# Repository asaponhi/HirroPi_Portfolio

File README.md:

このリポジトリは整理がされておらず、
リポジトリMaizuru_Portfolioを見ていただきたいです。

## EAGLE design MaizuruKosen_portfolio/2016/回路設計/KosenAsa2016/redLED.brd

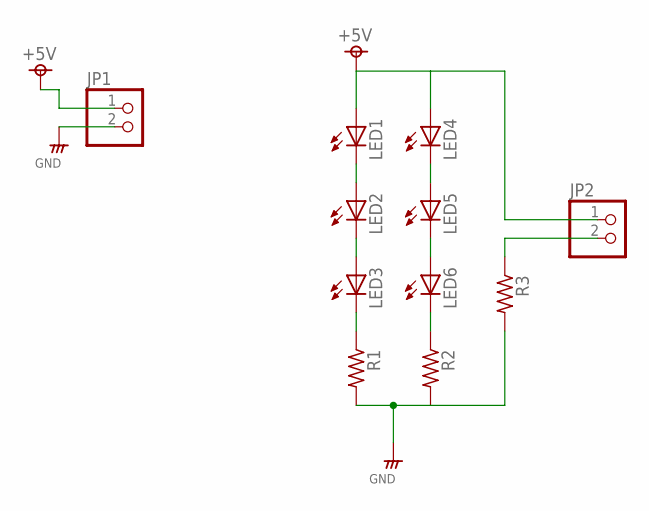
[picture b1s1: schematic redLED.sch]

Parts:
JP1, JP2: PINHD-1X2"; 1*02
LED1, LED2, LED3, LED4, LED5, LED6: LED5MM
R1, R2: RESISTORS-3; R_0.2
R3: RESISTORS-4; R_0.3

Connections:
+5V: JP1.1, JP2.1, LED1.A, LED4.A
GND: JP1.2, R1.2, R2.2, R3.2
unnamed: JP2.2, R3.1
unnamed: LED3.K (C), R1.1
unnamed: LED1.K (C), LED2.A
unnamed: LED2.K (C), LED3.A
unnamed: LED6.K (C), R2.1
unnamed: LED4.K (C), LED5.A
unnamed: LED5.K (C), LED6.A

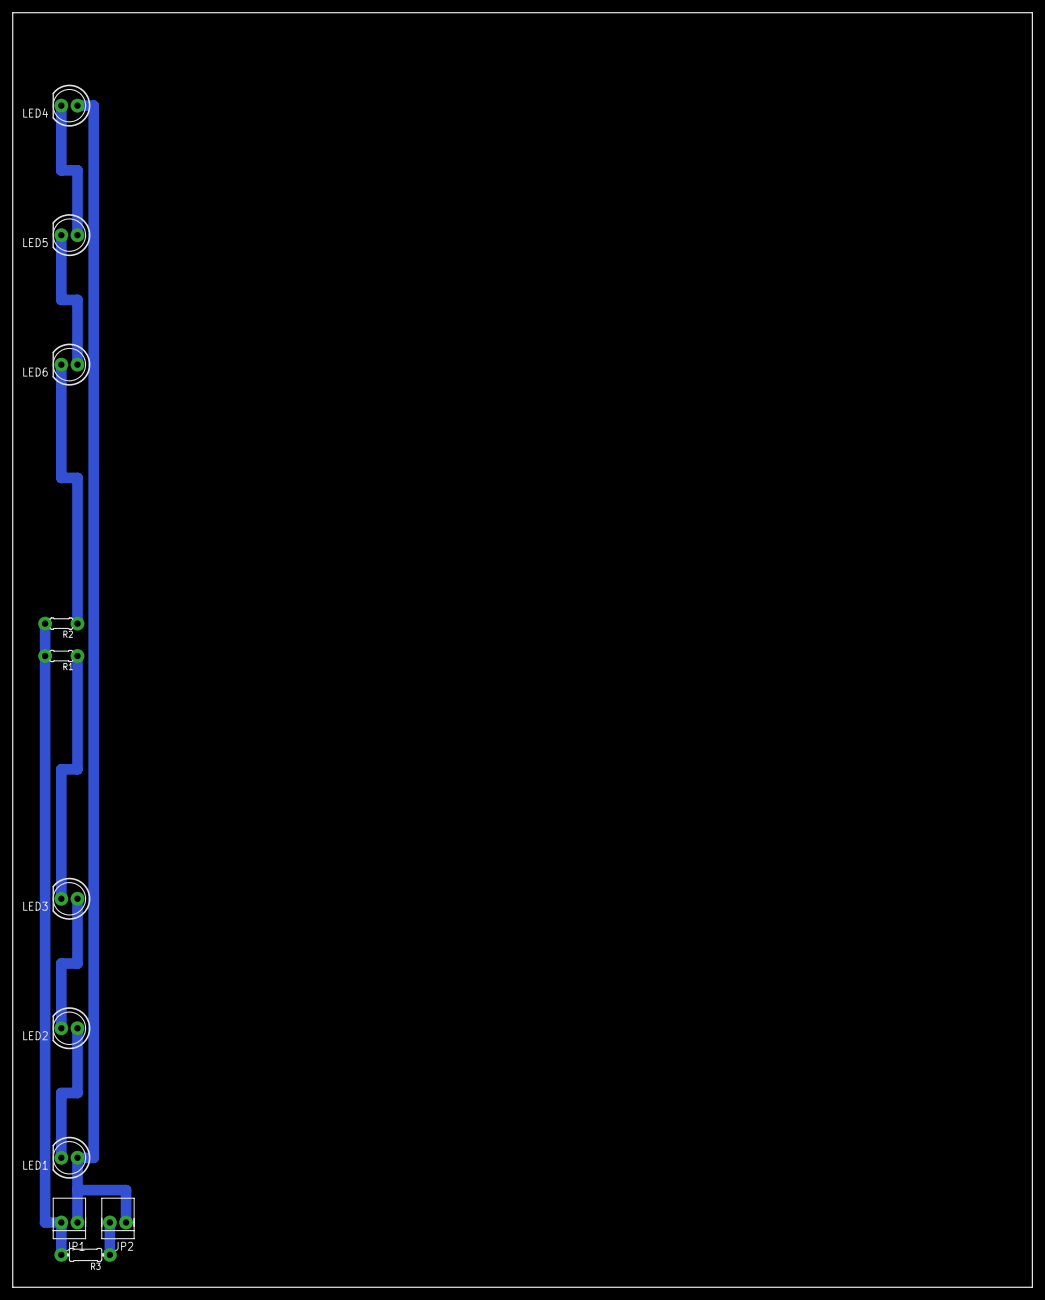
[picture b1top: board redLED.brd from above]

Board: 2 copper layers, 160.0 x 200.0 mm, 11 parts (0 on the bottom side), 9 nets.

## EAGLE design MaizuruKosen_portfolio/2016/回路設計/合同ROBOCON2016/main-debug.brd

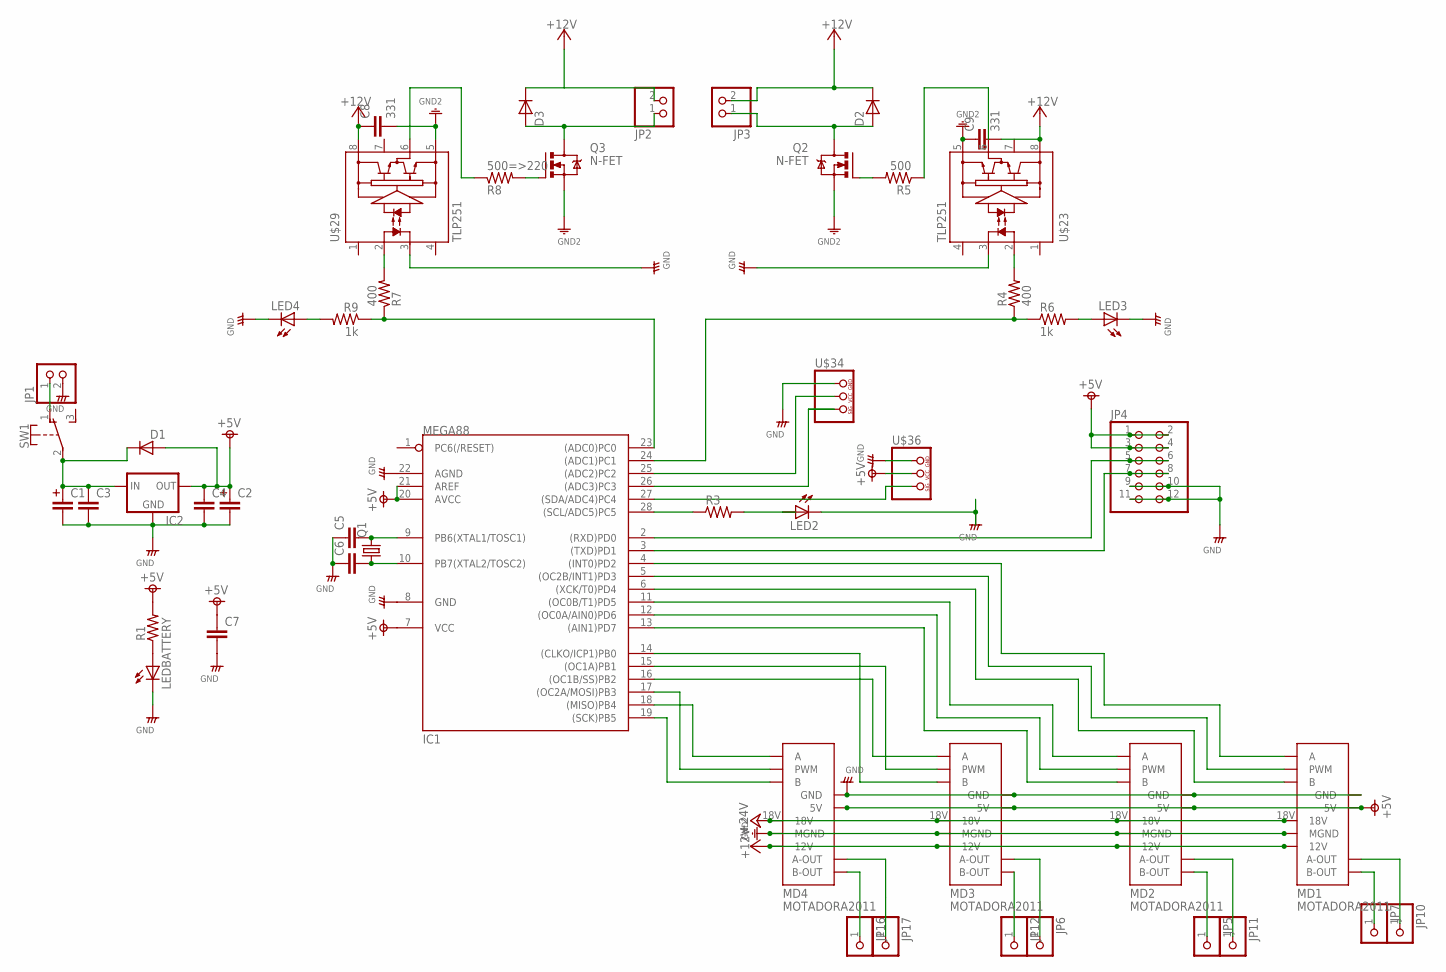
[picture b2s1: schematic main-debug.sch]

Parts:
C1, C2: CAPACITOR-330U; C_330U
C3, C4: MLCC-3; MLCC_50
C5, C6, C7: MLCC-2; MLCC_25
C8, C9: 331; MLCC_50
D1: DIODE_3
D2, D3: DIODE_4
IC1: MEGA88; DIL28-3
IC2: 78; 78XX
JP1: PINHD-1X2"; 1*02
JP2, JP3: PINHD-1X2; 1X02
JP4: PINHD-2X6; 2X06
JP5, JP6, JP7, JP10, JP11, JP12, JP16, JP17: PINHD-1X1; 1X01
LED2, LED3, LED4: LED5MM
LEDBATTERY: LED5MM
MD1, MD2, MD3, MD4: MOTADORA2011; MOTADORA2010
Q1: CTYSTALHC49/S; HC49/S
Q2, Q3: N-FET; TO-220V
R1, R3: RESISTORS-3; R_0.3
R4, R7: 400; R_0.3
R5: 500; R_0.3
R6, R9: 1k; R_0.3
R8: 500=>220; R_0.3
SW1: TOGGLE; 9450-2
U$23, U$29: TLP251; DIP8
U$34, U$36: PINHD-SENSOR; 1*03(KIKAKU)

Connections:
+5V: C2.P$1 (1), C4.1, C7.1, D1.A, IC1.7 (VCC), IC1.20 (AVCC), IC1.21 (AREF), IC2.P$3 (OUT), JP4.1, JP4.2, JP4.3, JP4.4, MD1.5V, MD2.5V, MD3.5V, MD4.5V, R1.2, U$36.VCC
+12V: C8.1, C9.2, D2.C, D3.C, JP2.2, JP3.2, MD1.12V, MD2.12V, MD3.12V, MD4.12V, U$23.8, U$29.8
+24V: MD1.18V, MD2.18V, MD3.18V, MD4.18V
GND: C1.P$2 (2), C2.P$2 (2), C3.2, C4.2, C5.1, C6.1, C7.2, IC1.8 (GND), IC1.22 (AGND), IC2.P$2 (GND), JP1.2, JP4.9, JP4.10, JP4.11, JP4.12, LED2.K (C), LED3.K (C), LED4.K (C), LEDBATTERY.K (C), MD1.GND, MD2.GND, MD3.GND, MD4.GND, U$23.3, U$29.3, U$34.GND, U$36.GND
GND12: C8.2, C9.1, MD1.MGND, MD2.MGND, MD3.MGND, MD4.MGND, Q2.3 (S), Q3.3 (S), U$23.5, U$29.5
unnamed: C5.2, IC1.9 (PB6(XTAL1/TOSC1)), Q1.2
unnamed: C6.2, IC1.10 (PB7(XTAL2/TOSC2)), Q1.1
unnamed: JP1.1, SW1.1 (O)
unnamed: C1.P$1 (1), C3.1, D1.C, IC2.P$1 (IN), SW1.2
unnamed: IC1.27 ((SDA/ADC4)PC4), U$36.SIG
unnamed: IC1.23 ((ADC0)PC0), R7.1, R9.1
unnamed: IC1.24 ((ADC1)PC1), R4.1, R6.1
unnamed: IC1.2 ((RXD)PD0), JP4.5, JP4.6
unnamed: IC1.18 ((MISO)PB4), MD4.A
unnamed: IC1.6 ((XCK/T0)PD4), MD1.B
unnamed: IC1.4 ((INT0)PD2), MD1.A
unnamed: IC1.19 ((SCK)PB5), MD4.B
unnamed: IC1.3 ((TXD)PD1), JP4.7, JP4.8
unnamed: IC1.28 ((SCL/ADC5)PC5), R3.1
unnamed: IC1.5 ((OC2B/INT1)PD3), MD1.PWM
unnamed: IC1.17 ((OC2A/MOSI)PB3), MD4.PWM
unnamed: IC1.16 ((OC1B/SS)PB2), MD3.A
unnamed: IC1.15 ((OC1A)PB1), MD3.PWM
unnamed: IC1.14 ((CLKO/ICP1)PB0), MD3.B
unnamed: IC1.13 ((AIN1)PD7), MD2.B
unnamed: IC1.12 ((OC0A/AIN0)PD6), MD2.PWM
unnamed: IC1.11 ((OC0B/T1)PD5), MD2.A
unnamed: JP12.1, MD3.B-OUT
unnamed: JP6.1, MD3.A-OUT
unnamed: JP11.1, MD2.A-OUT
unnamed: JP7.1, MD1.B-OUT
unnamed: JP10.1, MD1.A-OUT
unnamed: D3.A, JP2.1, Q3.2 (D)
unnamed: Q2.1 (G), R5.2
unnamed: JP5.1, MD2.B-OUT
unnamed: JP16.1, MD4.B-OUT
unnamed: JP17.1, MD4.A-OUT
unnamed: D2.A, JP3.1, Q2.2 (D)
unnamed: R4.2, U$23.2
unnamed: R5.1, U$23.6
unnamed: LED3.A, R6.2
unnamed: LEDBATTERY.A, R1.1
unnamed: Q3.1 (G), R8.2
unnamed: IC1.25 ((ADC2)PC2), U$34.VCC
unnamed: R7.2, U$29.2
unnamed: R8.1, U$29.6
unnamed: LED4.A, R9.2
unnamed: IC1.26 ((ADC3)PC3), U$34.SIG
unnamed: LED2.A, R3.2

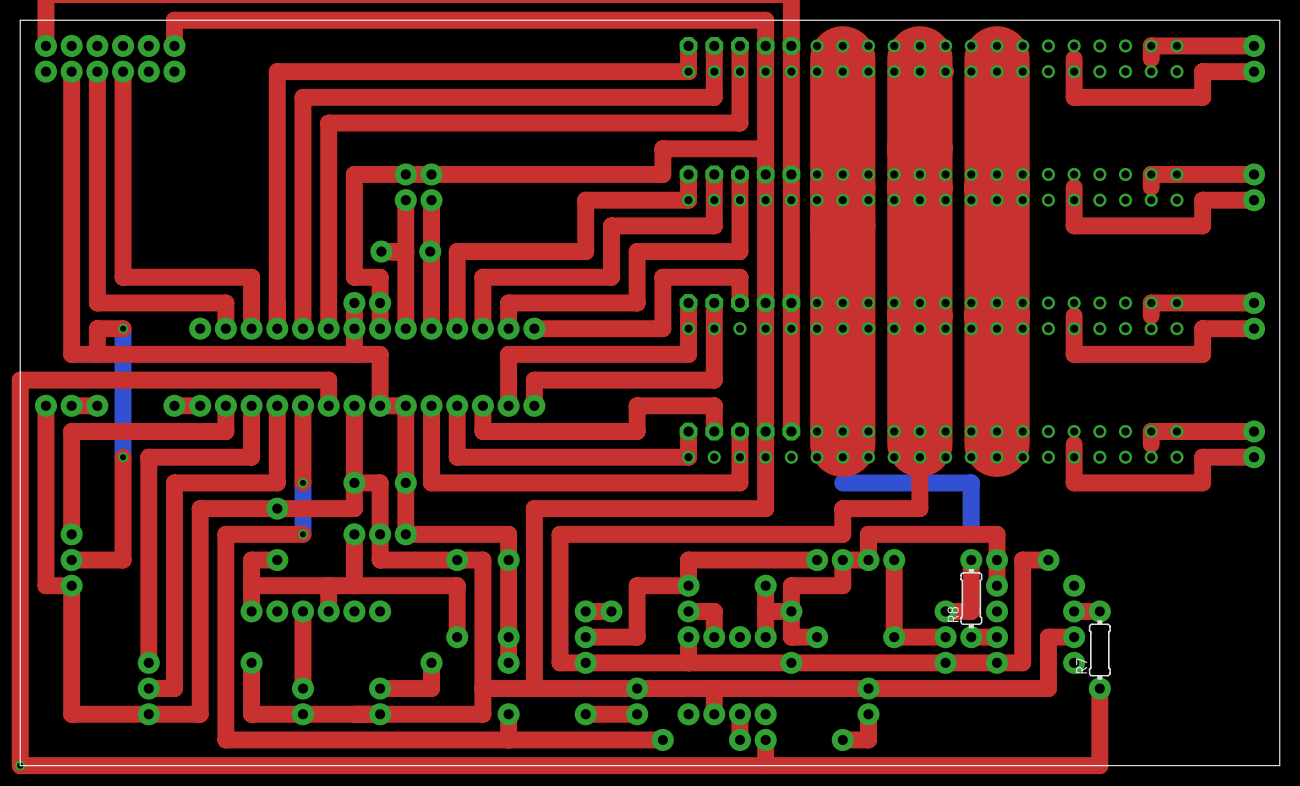
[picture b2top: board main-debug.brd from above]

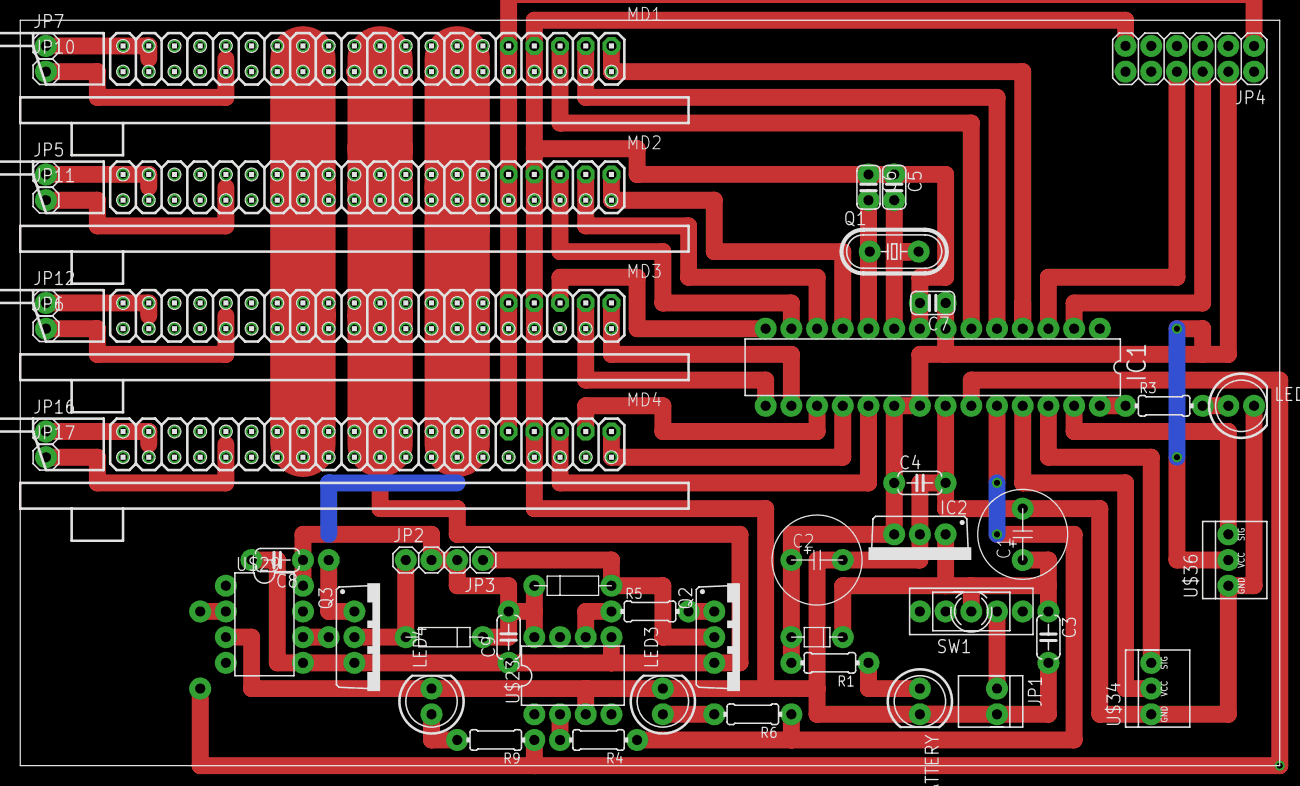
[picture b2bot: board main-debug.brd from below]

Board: 2 copper layers, 124.5 x 73.7 mm, 50 parts (48 on the bottom side), 49 nets.

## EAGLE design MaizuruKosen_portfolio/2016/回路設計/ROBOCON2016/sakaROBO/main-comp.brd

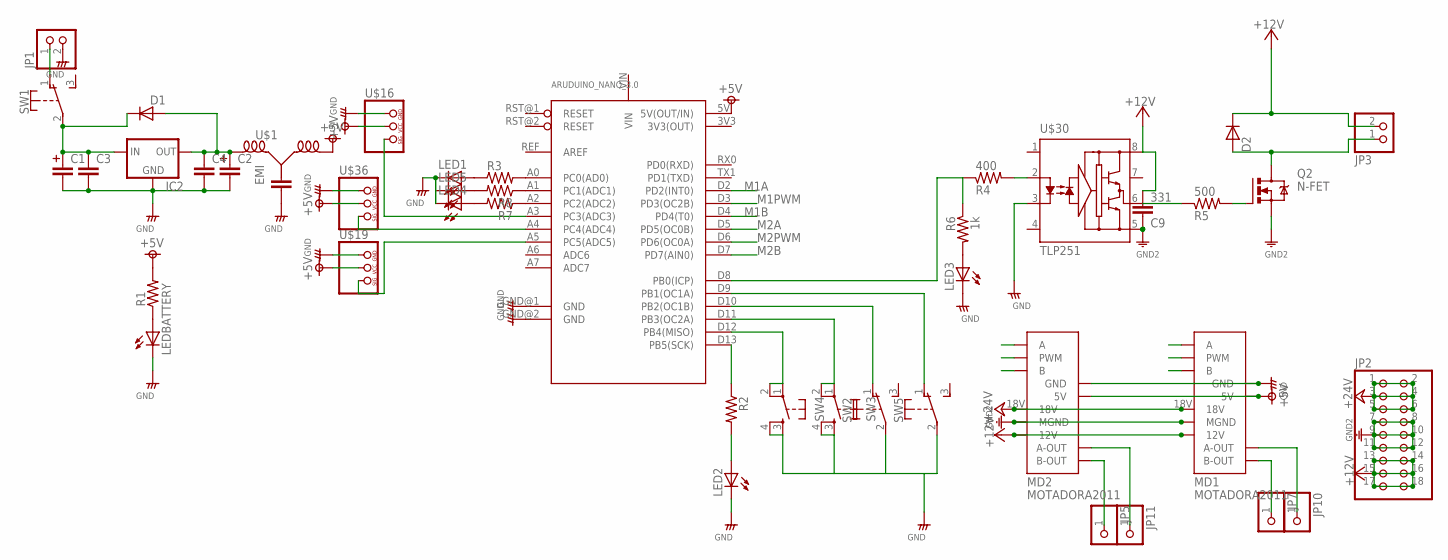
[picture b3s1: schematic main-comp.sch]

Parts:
C1, C2: CAPACITOR-330U; C_330U
C3, C4: MLCC-3; MLCC_50
C9: 331; MLCC_50
D1: DIODE_3
D2: DIODE_4
IC2: 78; 78XX
JP1: PINHD-1X2"; 1*02
JP2: PINHD-2X9; 2X09
JP3: PINHD-1X2; 1X02
JP5, JP7, JP10, JP11: PINHD-1X1; 1X01
LED1, LED2, LED3, LED4, LED5: LED3MM
LEDBATTERY: LED5MM
MD1, MD2: MOTADORA2011; MOTADORA2010
Q2: N-FET; TO-220V
R1: RESISTORS-2; R_0.2
R2, R3, R7, R8: RESISTORS3216; 3216
R4: 400; R_0.2
R5: 500; 3216
R6: 1k; 3216
SW1, SW2, SW5: TOGGLE; 9450-2
SW3, SW4: TACTB3F; B3F-10XX
U$1: EMI; EMI_3
U$14: ARUDUINO_NANO_3.0; ARYDUINO_NANO_3.0
U$16, U$19, U$36: PINHD-SENSOR; 1*03(KIKAKU)
U$30: TLP251; DIP8

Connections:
+5V: MD1.5V, MD2.5V, R1.2, U$1.3, U$14.5V (5V(OUT/IN)), U$16.VCC, U$19.VCC, U$36.VCC
+12V: C9.2, D2.C, JP2.13, JP2.14, JP2.15, JP2.16, JP2.17, JP2.18, JP3.2, MD1.12V, MD2.12V, U$30.8
+24V: JP2.1, JP2.2, JP2.3, JP2.4, JP2.5, JP2.6, MD1.18V, MD2.18V
GND: C1.P$2 (2), C2.P$2 (2), C3.2, C4.2, IC2.P$2 (GND), JP1.2, LED1.K (C), LED2.K (C), LED3.K (C), LED4.K (C), LED5.K (C), LEDBATTERY.K (C), MD1.GND, MD2.GND, SW2.2, SW3.3 (S), SW3.4 (S1), SW4.3 (S), SW4.4 (S1), SW5.2, U$1.2, U$14.GND@1 (GND), U$14.GND@2 (GND), U$16.GND, U$19.GND, U$30.3, U$36.GND
GND12: C9.1, JP2.7, JP2.8, JP2.9, JP2.10, JP2.11, JP2.12, MD1.MGND, MD2.MGND, Q2.3 (S), U$30.5
M1A: MD1.A, U$14.D2 (PD2(INT0))
M1B: MD1.B, U$14.D4 (PD4(T0))
M1PWM: MD1.PWM, U$14.D3 (PD3(OC2B))
M2A: MD2.A, U$14.D5 (PD5(OC0B))
M2B: MD2.B, U$14.D7 (PD7(AIN0))
M2PWM: MD2.PWM, U$14.D6 (PD6(OC0A))
unnamed: U$14.A3 (PC3(ADC3)), U$16.SIG
unnamed: R3.2, U$14.A0 (PC0(AD0))
unnamed: JP1.1, SW1.1 (O)
unnamed: U$14.A4 (PC4(ADC4)), U$36.SIG
unnamed: C1.P$1 (1), C3.1, D1.C, IC2.P$1 (IN), SW1.2
unnamed: U$14.A5 (PC5(ADC5)), U$19.SIG
unnamed: LED4.A, R7.2
unnamed: R4.1, R6.1, U$14.D8 (PB0(ICP))
unnamed: C2.P$1 (1), C4.1, D1.A, IC2.P$3 (OUT), U$1.1
unnamed: R8.1, U$14.A1 (PC1(ADC1))
unnamed: LED1.A, R3.1
unnamed: SW2.1 (O), U$14.D10 (PB2(OC1B))
unnamed: SW5.1 (O), U$14.D9 (PB1(OC1A))
unnamed: R2.1, U$14.D13 (PB5(SCK))
unnamed: R7.1, U$14.A2 (PC2(ADC2))
unnamed: SW4.1, SW4.2 (P1), U$14.D12 (PB4(MISO))
unnamed: LEDBATTERY.A, R1.1
unnamed: SW3.1, SW3.2 (P1), U$14.D11 (PB3(OC2A))
unnamed: LED2.A, R2.2
unnamed: LED5.A, R8.2
unnamed: JP11.1, MD2.A-OUT
unnamed: JP7.1, MD1.B-OUT
unnamed: JP10.1, MD1.A-OUT
unnamed: Q2.1 (G), R5.2
unnamed: JP5.1, MD2.B-OUT
unnamed: D2.A, JP3.1, Q2.2 (D)
unnamed: R4.2, U$30.2
unnamed: R5.1, U$30.6
unnamed: LED3.A, R6.2

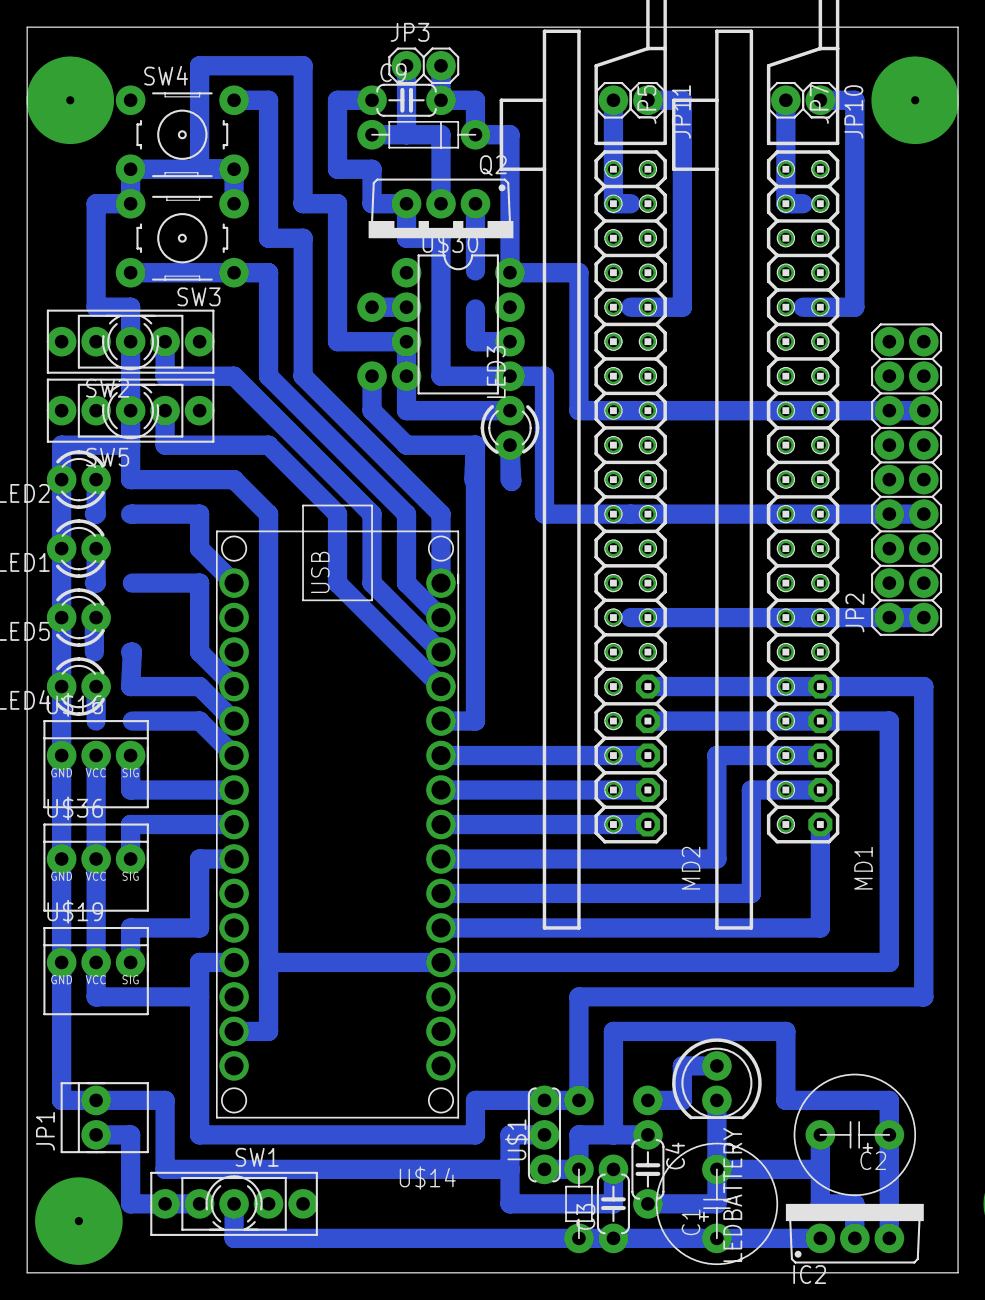
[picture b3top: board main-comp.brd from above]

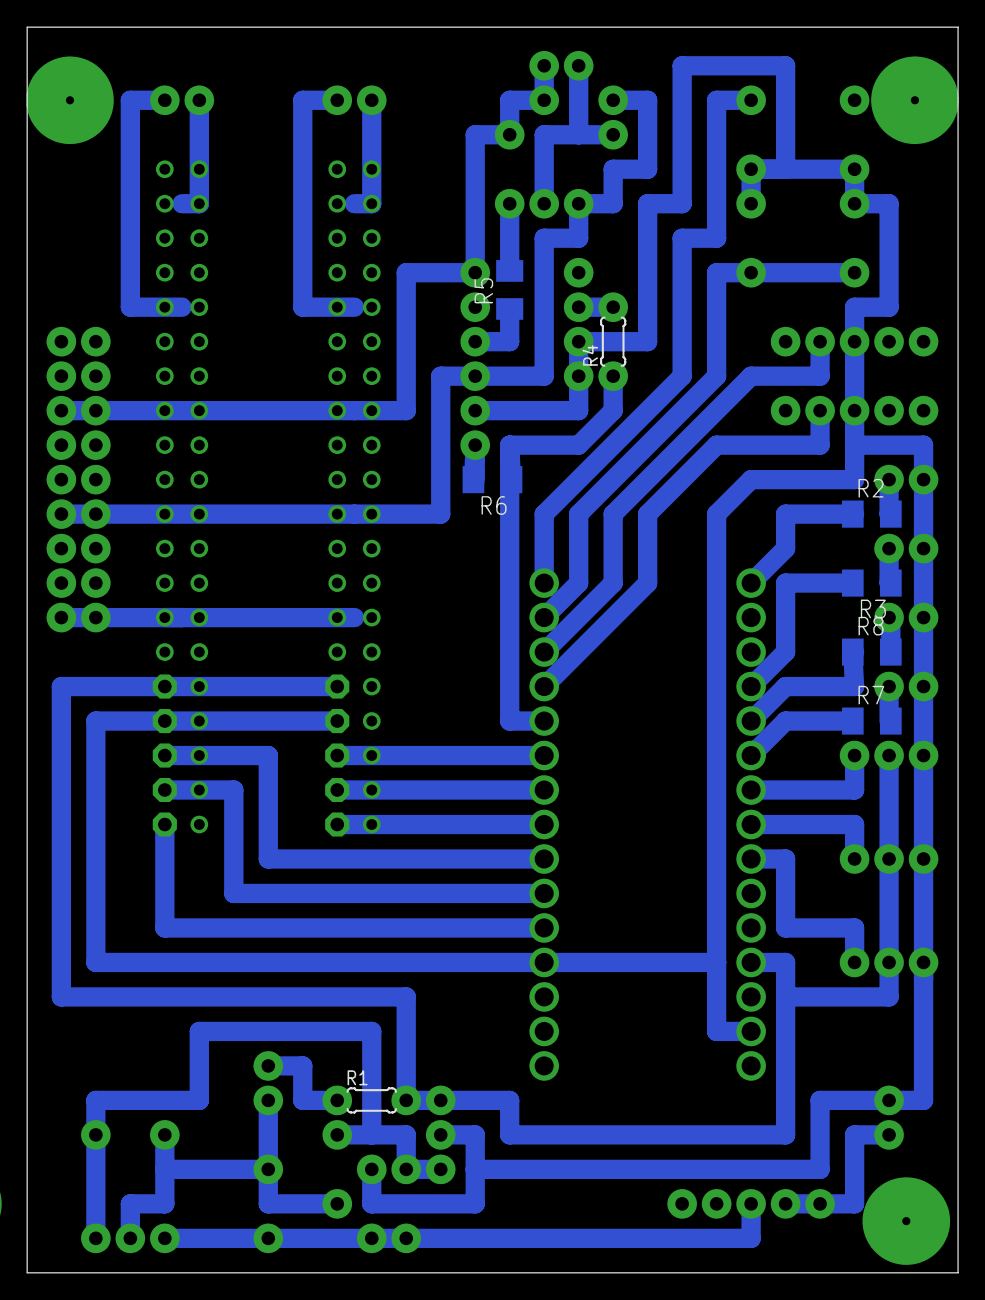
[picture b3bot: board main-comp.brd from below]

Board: 2 copper layers, 68.6 x 91.7 mm, 43 parts (8 on the bottom side), 40 nets.

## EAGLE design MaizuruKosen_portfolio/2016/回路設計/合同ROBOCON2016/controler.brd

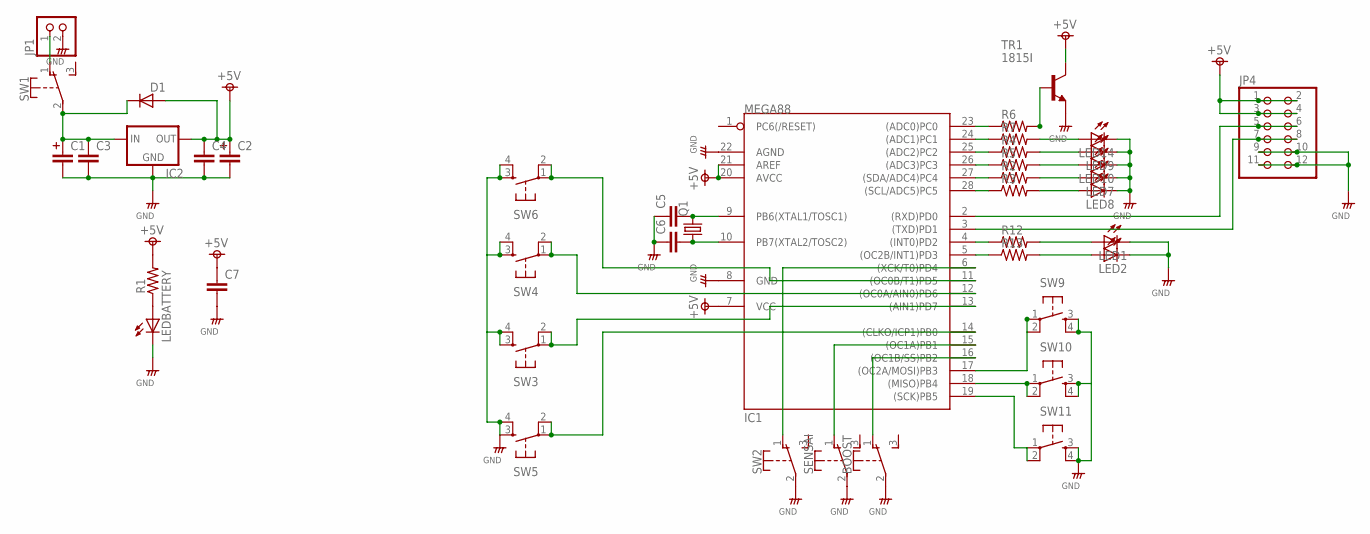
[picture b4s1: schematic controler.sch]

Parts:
BOOST: TOGGLE; 9450-2
C1, C2: CAPACITOR-330U; C_330U
C3, C4, C7: MLCC-3; MLCC_50
C5, C6: MLCC-2; MLCC_25
D1: DIODE_3
IC1: MEGA88; DIL28-3
IC2: 78; 78XX
JP1: PINHD-1X2"; 1*02
JP4: PINHD-2X6; 2X06
LED1, LED2, LED7, LED8, LED9, LED10, LED14: LED3MM
LEDBATTERY: LED5MM
Q1: CTYSTALHC49/S; HC49/S
R1, R6: RESISTORS-2; R_0.2
R2, R3, R4, R5, R7, R12, R13: RESISTORS-1; R_0.1
SENSAI: TOGGLE; 9450-2
SW1, SW2: TOGGLE; 9450-2
SW3, SW4, SW5, SW6, SW9, SW10, SW11: TACT; 1273
TR1: 1815I; TO92A

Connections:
+5V: C2.P$1 (1), C4.1, C7.1, D1.A, IC1.7 (VCC), IC1.20 (AVCC), IC1.21 (AREF), IC2.P$3 (OUT), JP4.1, JP4.2, JP4.3, JP4.4, R1.2, TR1.C
GND: BOOST.2, C1.P$2 (2), C2.P$2 (2), C3.2, C4.2, C5.1, C6.1, C7.2, IC1.8 (GND), IC1.22 (AGND), IC2.P$2 (GND), JP1.2, JP4.9, JP4.10, JP4.11, JP4.12, LED1.K (C), LED2.K (C), LED7.K (C), LED8.K (C), LED9.K (C), LED10.K (C), LED14.K (C), LEDBATTERY.K (C), SENSAI.2, SW2.2, SW3.3 (S), SW3.4 (S1), SW4.3 (S), SW4.4 (S1), SW5.3 (S), SW5.4 (S1), SW6.3 (S), SW6.4 (S1), SW9.3 (S), SW9.4 (S1), SW10.3 (S), SW10.4 (S1), SW11.3 (S), SW11.4 (S1), TR1.E
unnamed: C5.2, IC1.9 (PB6(XTAL1/TOSC1)), Q1.2
unnamed: C6.2, IC1.10 (PB7(XTAL2/TOSC2)), Q1.1
unnamed: JP1.1, SW1.1 (O)
unnamed: IC1.4 ((INT0)PD2), R12.1
unnamed: C1.P$1 (1), C3.1, D1.C, IC2.P$1 (IN), SW1.2
unnamed: IC1.5 ((OC2B/INT1)PD3), R13.1
unnamed: LED2.A, R13.2
unnamed: LED1.A, R12.2
unnamed: IC1.2 ((RXD)PD0), JP4.5, JP4.6
unnamed: IC1.25 ((ADC2)PC2), R4.1
unnamed: IC1.26 ((ADC3)PC3), R5.1
unnamed: R6.2, TR1.B
unnamed: IC1.23 ((ADC0)PC0), R6.1
unnamed: IC1.3 ((TXD)PD1), JP4.7, JP4.8
unnamed: IC1.27 ((SDA/ADC4)PC4), R2.1
unnamed: IC1.28 ((SCL/ADC5)PC5), R3.1
unnamed: IC1.24 ((ADC1)PC1), R7.1
unnamed: IC1.6 ((XCK/T0)PD4), SW2.1 (O)
unnamed: IC1.11 ((OC0B/T1)PD5), SW6.1, SW6.2 (P1)
unnamed: IC1.12 ((OC0A/AIN0)PD6), SW4.1, SW4.2 (P1)
unnamed: IC1.13 ((AIN1)PD7), SW3.1, SW3.2 (P1)
unnamed: IC1.14 ((CLKO/ICP1)PB0), SW5.1, SW5.2 (P1)
unnamed: IC1.18 ((MISO)PB4), SW10.1, SW10.2 (P1)
unnamed: IC1.15 ((OC1A)PB1), SENSAI.1 (O)
unnamed: BOOST.1 (O), IC1.16 ((OC1B/SS)PB2)
unnamed: IC1.17 ((OC2A/MOSI)PB3), SW9.1, SW9.2 (P1)
unnamed: IC1.19 ((SCK)PB5), SW11.1, SW11.2 (P1)
unnamed: LED8.A, R3.2
unnamed: LED10.A, R5.2
unnamed: LED14.A, R7.2
unnamed: LED7.A, R2.2
unnamed: LED9.A, R4.2
unnamed: LEDBATTERY.A, R1.1

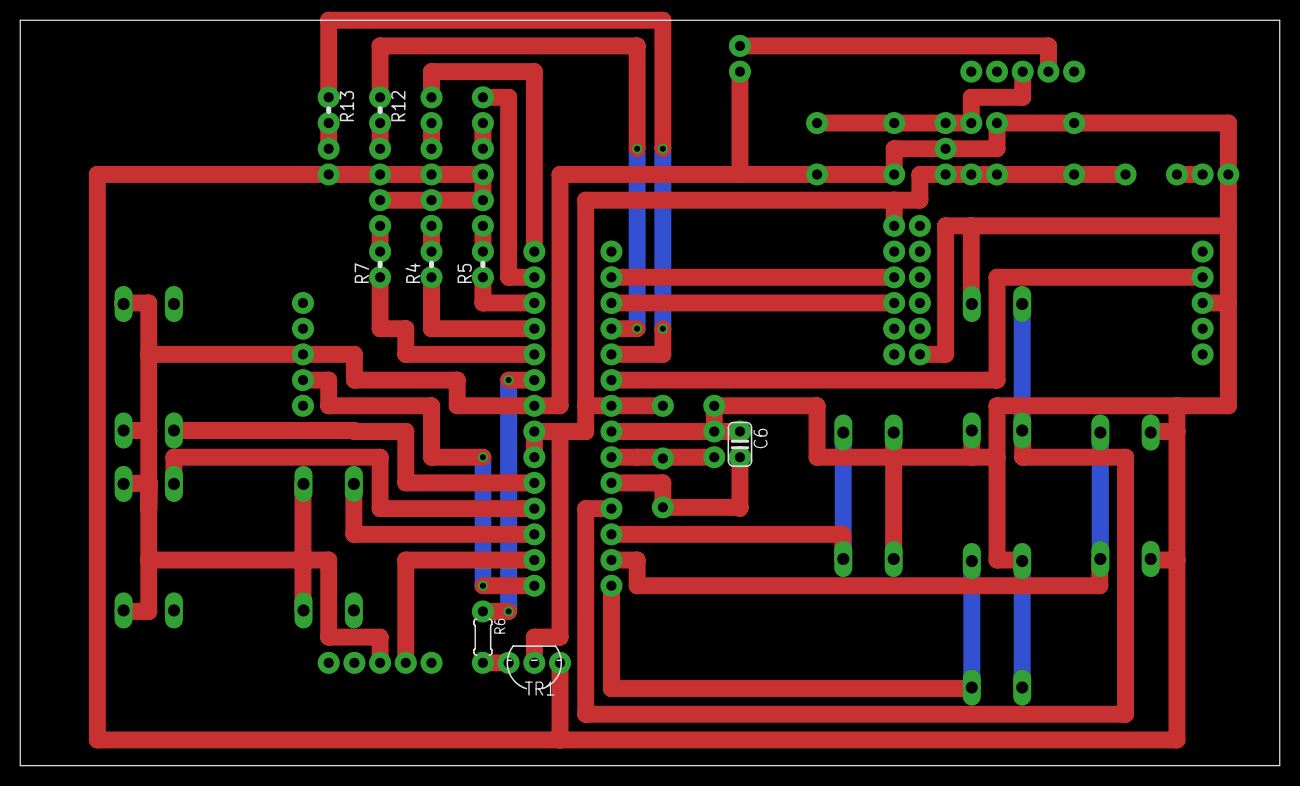
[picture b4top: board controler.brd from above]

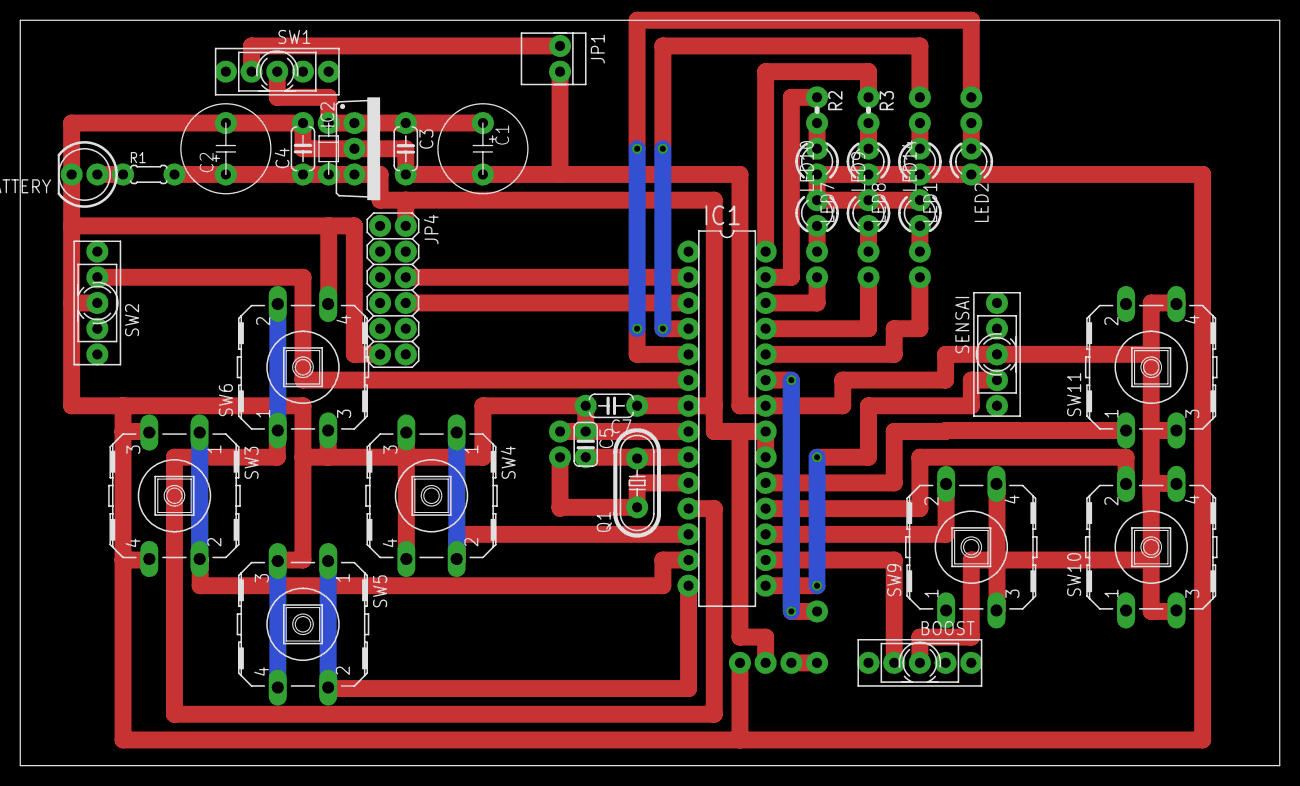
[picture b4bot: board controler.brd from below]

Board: 2 copper layers, 124.5 x 73.7 mm, 42 parts (34 on the bottom side), 35 nets.

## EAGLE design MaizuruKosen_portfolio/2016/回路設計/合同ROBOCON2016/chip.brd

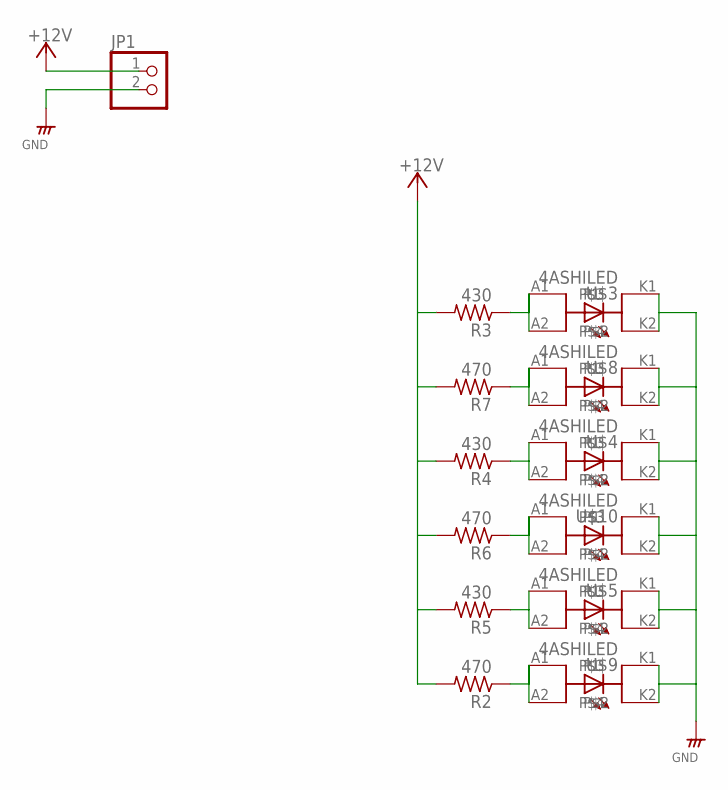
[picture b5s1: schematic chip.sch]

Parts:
JP1: PINHD-1X2"; 1*02
R2, R6, R7: 470; 3216
R3, R4, R5: 430; 3216
U$3, U$4, U$5, U$8, U$9, U$10: 4ASHILED; 4AHILED-KAI

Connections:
+12V: JP1.1, R2.2, R3.2, R4.2, R5.2, R6.2, R7.2
GND: JP1.2, U$3.K1, U$3.K2, U$4.K1, U$4.K2, U$5.K1, U$5.K2, U$8.K1, U$8.K2, U$9.K1, U$9.K2, U$10.K1, U$10.K2
unnamed: R7.1, U$8.A1 (P1), U$8.A2
unnamed: R3.1, U$3.A1 (P1), U$3.A2
unnamed: R4.1, U$4.A1 (P1), U$4.A2
unnamed: R5.1, U$5.A1 (P1), U$5.A2
unnamed: R6.1, U$10.A1 (P1), U$10.A2
unnamed: R2.1, U$9.A1 (P1), U$9.A2

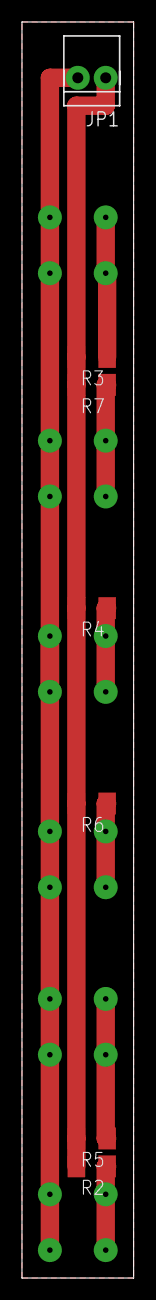
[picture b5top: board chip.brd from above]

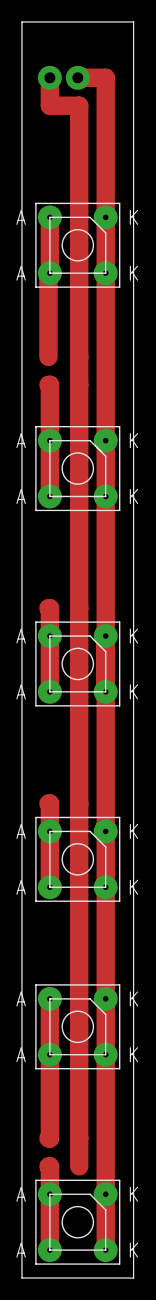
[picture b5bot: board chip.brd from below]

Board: 2 copper layers, 10.2 x 114.3 mm, 13 parts (6 on the bottom side), 8 nets.

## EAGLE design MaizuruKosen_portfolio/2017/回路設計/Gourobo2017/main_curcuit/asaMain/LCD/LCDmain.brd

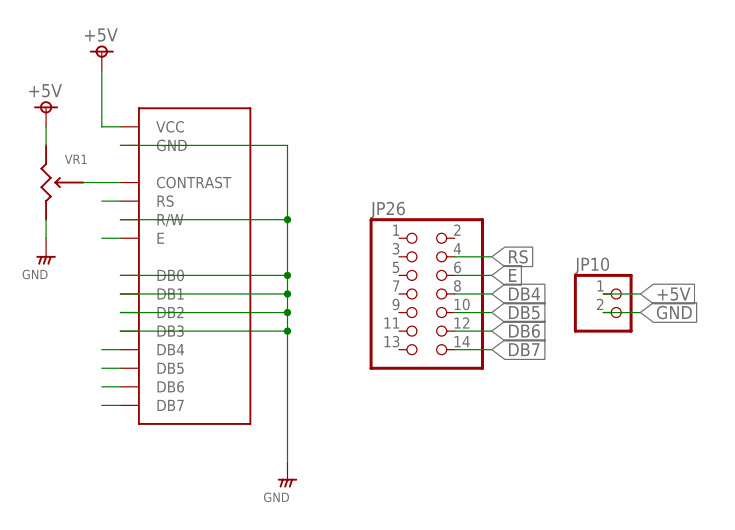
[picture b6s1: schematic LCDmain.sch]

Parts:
JP10: PINHD-1X2"; 1*02
JP26: PINHD-2X7; 2X07
U$1: LCD_16X2
VR1: R-TRIM-3-L; R_TRIM3

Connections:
+5V: JP10.1, U$1.P$1 (VCC), VR1.1
DB4: JP26.8, U$1.P$11 (DB4)
DB5: JP26.10, U$1.P$12 (DB5)
DB6: JP26.12, U$1.P$13 (DB6)
DB7: JP26.14, U$1.P$14 (DB7)
E: JP26.6, U$1.P$6 (E)
GND: JP10.2, U$1.P$2 (GND), U$1.P$5 (R/W), U$1.P$7 (DB0), U$1.P$8 (DB1), U$1.P$9 (DB2), U$1.P$10 (DB3), VR1.3
unnamed: U$1.P$3 (CONTRAST), VR1.2
RS: JP26.4, U$1.P$4 (RS)

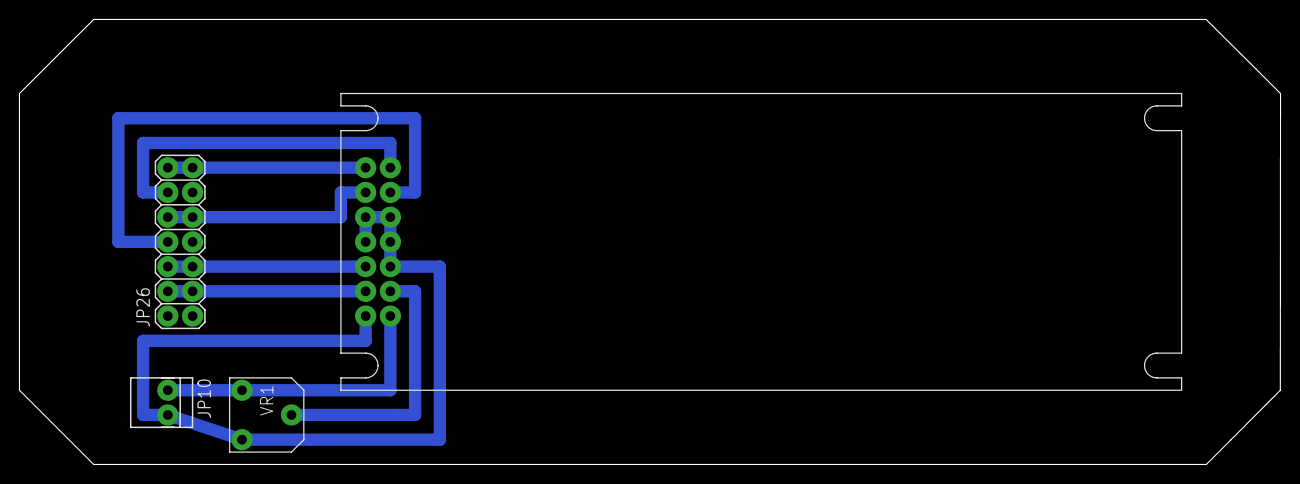
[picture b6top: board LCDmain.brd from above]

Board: 2 copper layers, 129.5 x 45.7 mm, 4 parts (0 on the bottom side), 9 nets.
